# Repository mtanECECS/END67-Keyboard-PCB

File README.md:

# END67 Keyboard PCB 
 First Keyboard PCB Design
 
#### END67 vOutFirst Files
 These files are the finished version of the PCB design. The gerbers are ready to be manufactured by PCB fabs.
 
#### END67 Files
 These files are the unfinished version of the design. The schematics and netlist should be complete, but the PCB has not been wired yet.

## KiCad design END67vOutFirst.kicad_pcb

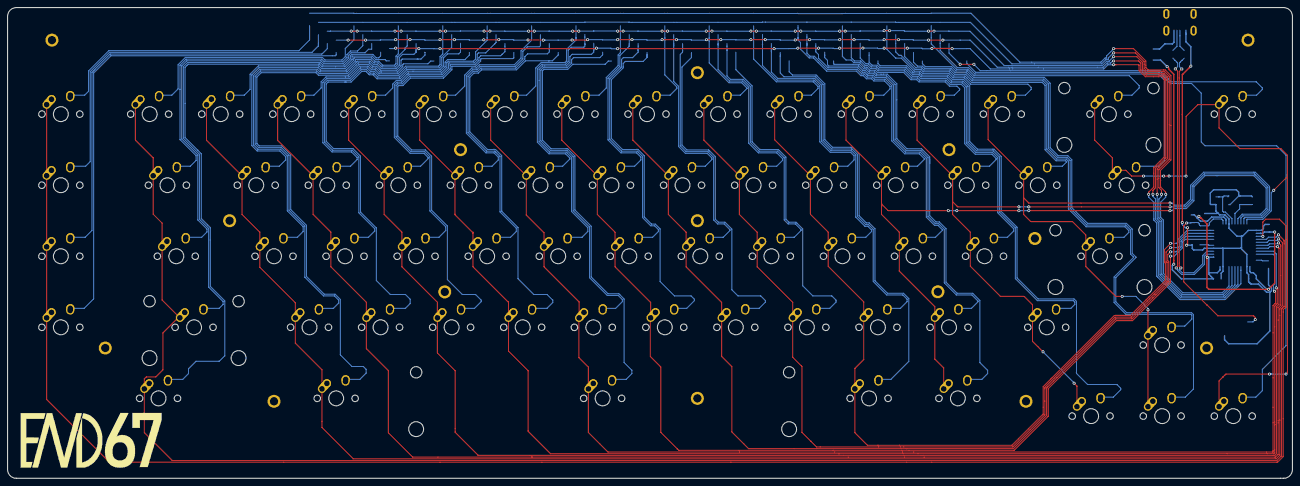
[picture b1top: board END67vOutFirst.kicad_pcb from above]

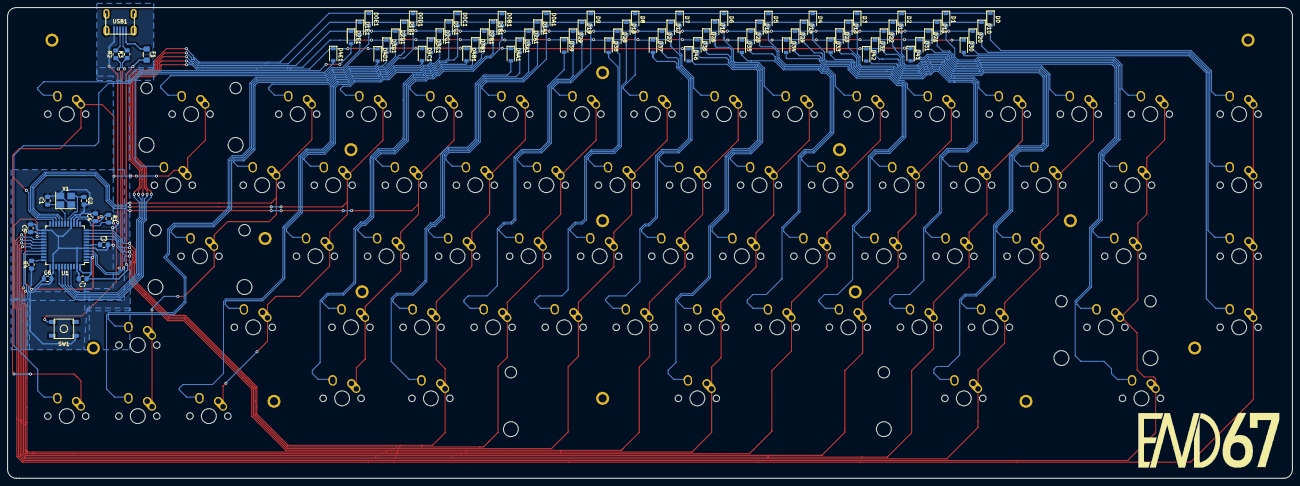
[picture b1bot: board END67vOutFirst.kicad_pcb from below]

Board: 2 copper layers, 344.5 x 126.2 mm, 150 parts (83 on the bottom side), 99 nets.

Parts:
C1, C2: 22pF; C_0805_2012Metric_Pad1.15x1.40mm_HandSolder
C3: 1uF; C_0805_2012Metric_Pad1.15x1.40mm_HandSolder
C4, C5, C6: 0.1uF; C_0805_2012Metric_Pad1.15x1.40mm_HandSolder
C7: 10uF; C_0805_2012Metric_Pad1.15x1.40mm_HandSolder
D0, D0A1, D0B1, D0C1, D0D1, D0E1, D1, D1A1, D1B1, D1C1, D1D1, D1E1, D2, D2A1, D2B1, D2C1, D2D1, D2E1, D3, D3A1, D3B1, D3C1, D3D1, D4, D4A1, D4B1, D4C1, D4D1, D4E1, D5, D6, D7, D8, D9, D10, D11, D12, D13, D14, D15, D16, D17, D18, D19, D20, D21, D22, D23, D24, D25, D26, D27, D28, D29, D30, D31, D32, D33, D34, D35, D36, D37, D38, D39, D41, D42, D46: D_Small; D_SOD-123
F1: 500mA; Fuse_1206_3216Metric_Pad1.42x1.75mm_HandSolder
MX0, MX0A1, MX0B1, MX0C1, MX0D1, MX1, MX1A1, MX1B1, MX1C1, MX1D1, MX2, MX2A1, MX2B1, MX2C1, MX2E1, MX3, MX3A1, MX3B1, MX3D1, MX4, MX4C1, MX4D1, MX4E1, MX5, MX6, MX7, MX8, MX9, MX10, MX12, MX13, MX14, MX15, MX16, MX17, MX18, MX19, MX20, MX22, MX23, MX24, MX25, MX26, MX27, MX28, MX29, MX30, MX32, MX33, MX34, MX35, MX36, MX37, MX38, MX39: MX-NoLED; MX-1U-NoLED
MX0E1: MX-NoLED; MX-2U-NoLED
MX1E1, MX11: MX-NoLED; MX-1.5U-NoLED
MX2D1, MX31: MX-NoLED; MX-2.25U-NoLED
MX3C1, MX21: MX-NoLED; MX-1.75U-NoLED
MX4A1, MX4B1, MX41, MX42: MX-NoLED; MX-1.25U-NoLED
MX46: MX-NoLED; MX-6.25U-NoLED
R1, R4: 10k; R_0805_2012Metric_Pad1.15x1.40mm_HandSolder
R2, R3: 22; R_0805_2012Metric_Pad1.15x1.40mm_HandSolder
SW1: SW_Push; SKQG-1155865
U1: ATmega32U4-AU; TQFP-44_10x10mm_P0.8mm
USB1: Molex-0548190589
Y1: 16MHz; Crystal_SMD_3225-4Pin_3.2x2.5mm_HandSoldering

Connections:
+5V: C4.1, C5.1, C6.1, C7.1, F1.2, R1.1, U1.2, U1.7, U1.14, U1.24, U1.34, U1.44
COL0: MX0.1, MX10.1, MX20.1, MX30.1, U1.25
COL1: MX1.1, MX11.1, MX21.1, MX31.1, MX41.1, U1.26
COL2: MX2.1, MX12.1, MX22.1, MX32.1, MX42.1, U1.27
COL3: MX3.1, MX13.1, MX23.1, MX33.1, U1.28
COL4: MX4.1, MX14.1, MX24.1, MX34.1, U1.29
COL5: MX5.1, MX15.1, MX25.1, MX35.1, U1.30
COL6: MX6.1, MX16.1, MX26.1, MX36.1, MX46.1, U1.31
COL7: MX7.1, MX17.1, MX27.1, MX37.1, U1.8
COL8: MX8.1, MX18.1, MX28.1, MX38.1, U1.9
COL9: MX9.1, MX19.1, MX29.1, MX39.1, U1.10
COL10: MX0A1.1, MX1A1.1, MX2A1.1, MX3A1.1, MX4A1.1, U1.11
COL11: MX0B1.1, MX1B1.1, MX2B1.1, MX3B1.1, MX4B1.1, U1.18
COL12: MX0C1.1, MX1C1.1, MX2C1.1, MX3C1.1, MX4C1.1, U1.19
COL13: MX0D1.1, MX1D1.1, MX2D1.1, MX3D1.1, MX4D1.1, U1.20
COL14: MX0E1.1, MX1E1.1, MX2E1.1, MX4E1.1, U1.21
D+: R2.2, USB1.3
D-: R3.2, USB1.4
GND: C1.2, C2.2, C3.2, C4.2, C5.2, C6.2, C7.2, R4.1, SW1.1, U1.5, U1.15, U1.23, U1.35, U1.43, USB1.1, Y1.2, Y1.4
unnamed: C1.1, U1.17, Y1.1
unnamed: C2.1, U1.16, Y1.3
unnamed: C3.1, U1.6
unnamed: D0.2, MX0.2
unnamed: D0A1.2, MX0A1.2
unnamed: D0B1.2, MX0B1.2
unnamed: D0C1.2, MX0C1.2
unnamed: D0D1.2, MX0D1.2
unnamed: D0E1.2, MX0E1.2
unnamed: D1.2, MX1.2
unnamed: D1A1.2, MX1A1.2
unnamed: D1B1.2, MX1B1.2
unnamed: D1C1.2, MX1C1.2
unnamed: D1D1.2, MX1D1.2
unnamed: D1E1.2, MX1E1.2
unnamed: D2.2, MX2.2
unnamed: D2A1.2, MX2A1.2
unnamed: D2B1.2, MX2B1.2
unnamed: D2C1.2, MX2C1.2
unnamed: D2D1.2, MX2D1.2
unnamed: D2E1.2, MX2E1.2
unnamed: D3.2, MX3.2
unnamed: D3A1.2, MX3A1.2
unnamed: D3B1.2, MX3B1.2
unnamed: D3C1.2, MX3C1.2
unnamed: D3D1.2, MX3D1.2
unnamed: D4.2, MX4.2
unnamed: D4A1.2, MX4A1.2
unnamed: D4B1.2, MX4B1.2
unnamed: D4C1.2, MX4C1.2
unnamed: D4D1.2, MX4D1.2
unnamed: D4E1.2, MX4E1.2
unnamed: D5.2, MX5.2
unnamed: D6.2, MX6.2
unnamed: D7.2, MX7.2
unnamed: D8.2, MX8.2
unnamed: D9.2, MX9.2
unnamed: D10.2, MX10.2
unnamed: D11.2, MX11.2
unnamed: D12.2, MX12.2
unnamed: D13.2, MX13.2
unnamed: D14.2, MX14.2
unnamed: D15.2, MX15.2
unnamed: D16.2, MX16.2
unnamed: D17.2, MX17.2
unnamed: D18.2, MX18.2
unnamed: D19.2, MX19.2
unnamed: D20.2, MX20.2
unnamed: D21.2, MX21.2
unnamed: D22.2, MX22.2
unnamed: D23.2, MX23.2
unnamed: D24.2, MX24.2
unnamed: D25.2, MX25.2
unnamed: D26.2, MX26.2
unnamed: D27.2, MX27.2
unnamed: D28.2, MX28.2
unnamed: D29.2, MX29.2
unnamed: D30.2, MX30.2
unnamed: D31.2, MX31.2
unnamed: D32.2, MX32.2
unnamed: D33.2, MX33.2
unnamed: D34.2, MX34.2
unnamed: D35.2, MX35.2
unnamed: D36.2, MX36.2
unnamed: D37.2, MX37.2
unnamed: D38.2, MX38.2
unnamed: D39.2, MX39.2
unnamed: D41.2, MX41.2
unnamed: D42.2, MX42.2
unnamed: D46.2, MX46.2
unnamed: R1.2, SW1.2, U1.13
unnamed: R2.1, U1.4
unnamed: R3.1, U1.3
unnamed: R4.2, U1.33
ROW0: D0.1, D0A1.1, D0B1.1, D0C1.1, D0D1.1, D0E1.1, D1.1, D2.1, D3.1, D4.1, D5.1, D6.1, D7.1, D8.1, D9.1, U1.41
ROW1: D1A1.1, D1B1.1, D1C1.1, D1D1.1, D1E1.1, D10.1, D11.1, D12.1, D13.1, D14.1, D15.1, D16.1, D17.1, D18.1, D19.1, U1.40
ROW2: D2A1.1, D2B1.1, D2C1.1, D2D1.1, D2E1.1, D20.1, D21.1, D22.1, D23.1, D24.1, D25.1, D26.1, D27.1, D28.1, D29.1, U1.39
ROW3: D3A1.1, D3B1.1, D3C1.1, D3D1.1, D30.1, D31.1, D32.1, D33.1, D34.1, D35.1, D36.1, D37.1, D38.1, D39.1, U1.38
ROW4: D4A1.1, D4B1.1, D4C1.1, D4D1.1, D4E1.1, D41.1, D42.1, D46.1, U1.37
VCC: F1.1, USB1.5

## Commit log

2019-10-31 Created PCB Files
2019-10-31 Add submodules
2019-10-31 Updated submodules
2019-10-31 Updated Libs
2019-11-01 updated schematics
2019-11-01 Updated Kicad libs
2019-11-10 Finished Layout
2019-11-13 Finished First Prototype
2020-01-14 Updated Files
